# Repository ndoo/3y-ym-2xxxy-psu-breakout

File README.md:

# 3y-ym-2xxxy-psu-breakout

Breakout for 3Y YM-2xxxY series power supply modules

It should also work for any other 50.5mm wide power supply modules from 3Y/FSP, that use PCB finger connectors.

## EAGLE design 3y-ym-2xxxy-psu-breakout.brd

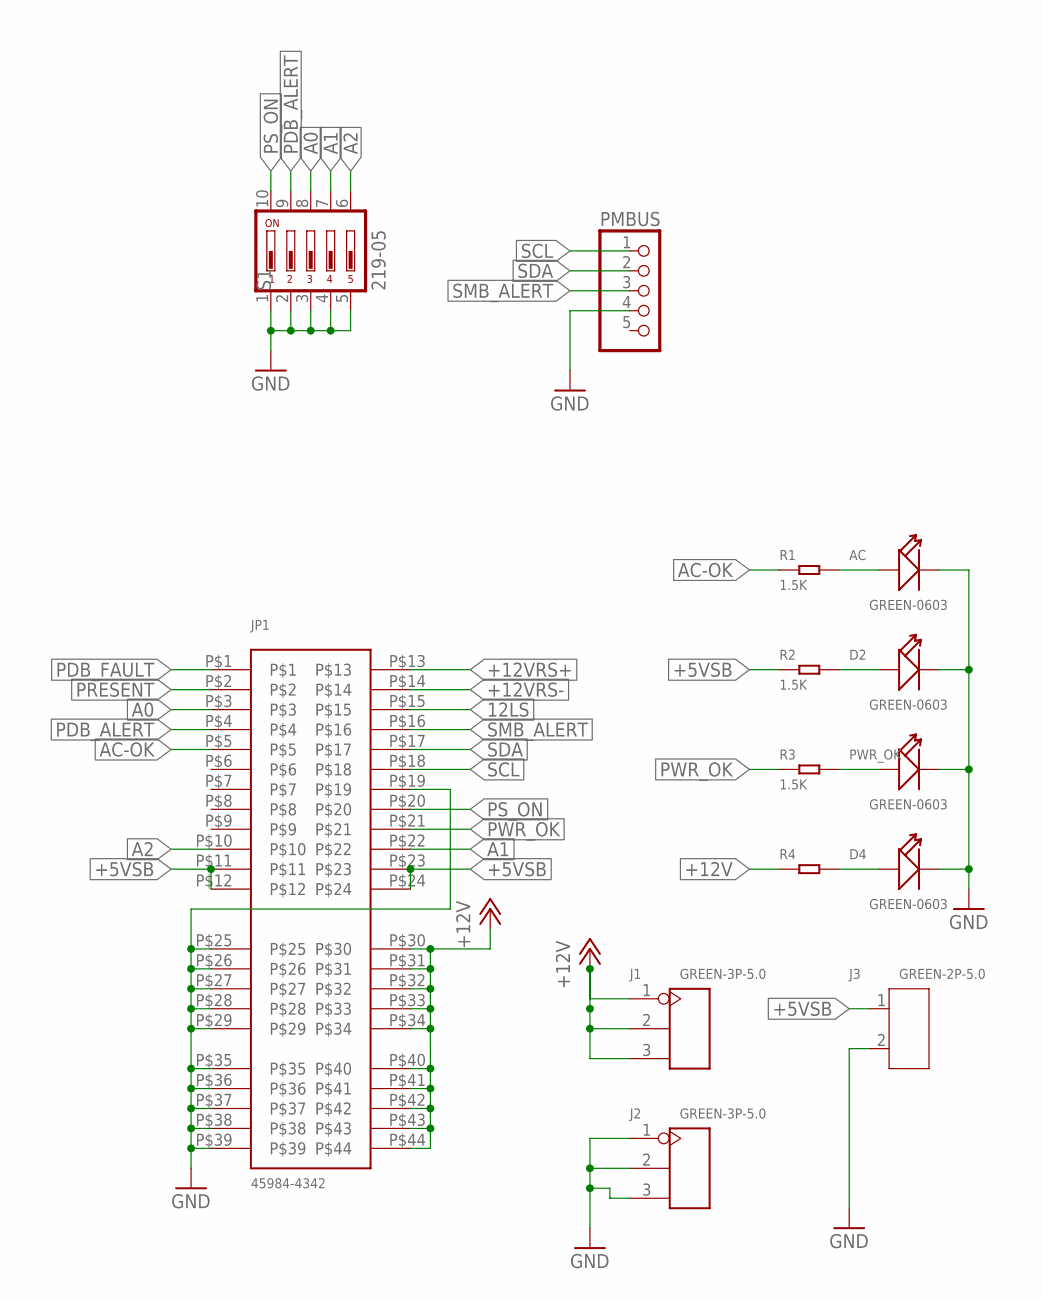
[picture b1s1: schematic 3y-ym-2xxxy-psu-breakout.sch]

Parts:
AC: GREEN-0603; LED-0603
D2, D4: GREEN-0603; LED-0603
J1, J2: GREEN-3P-5.0; H3-5.0-15.5X8.0MM
J3: GREEN-2P-5.0; H2-5.0-10.5X8.0MM
JP1: 45984-4342
PMBUS: PINHD-1X5; 1X05
PWR_OK: GREEN-0603; LED-0603
R1, R2, R3, R4: 1.5K; R0603
S1: 219-05; CTS-219-05

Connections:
12LS: JP1.P$15
+5VSB: J3.1, JP1.P$11, JP1.P$12, JP1.P$23, JP1.P$24, R2.1
+12V: J1.1, J1.2, J1.3, JP1.P$30, JP1.P$31, JP1.P$32, JP1.P$33, JP1.P$34, JP1.P$40, JP1.P$41, JP1.P$42, JP1.P$43, JP1.P$44, R4.1
+12VRS+: JP1.P$13
+12VRS-: JP1.P$14
A0: JP1.P$3, S1.8
A1: JP1.P$22, S1.7
A2: JP1.P$10, S1.6
AC-OK: JP1.P$5, R1.1
GND: AC.-, D2.-, D4.-, J2.1, J2.2, J2.3, J3.2, JP1.P$19, JP1.P$25, JP1.P$26, JP1.P$27, JP1.P$28, JP1.P$29, JP1.P$35, JP1.P$36, JP1.P$37, JP1.P$38, JP1.P$39, PMBUS.4, PWR_OK.-, S1.1, S1.2, S1.3, S1.4, S1.5
unnamed: AC.+, R1.2
unnamed: D2.+, R2.2
unnamed: PWR_OK.+, R3.2
unnamed: D4.+, R4.2
PDB_ALERT: JP1.P$4, S1.9
PDB_FAULT: JP1.P$1
PRESENT: JP1.P$2
PS_ON: JP1.P$20, S1.10
PWR_OK: JP1.P$21, R3.1
SCL: JP1.P$18, PMBUS.1
SDA: JP1.P$17, PMBUS.2
SMB_ALERT: JP1.P$16, PMBUS.3

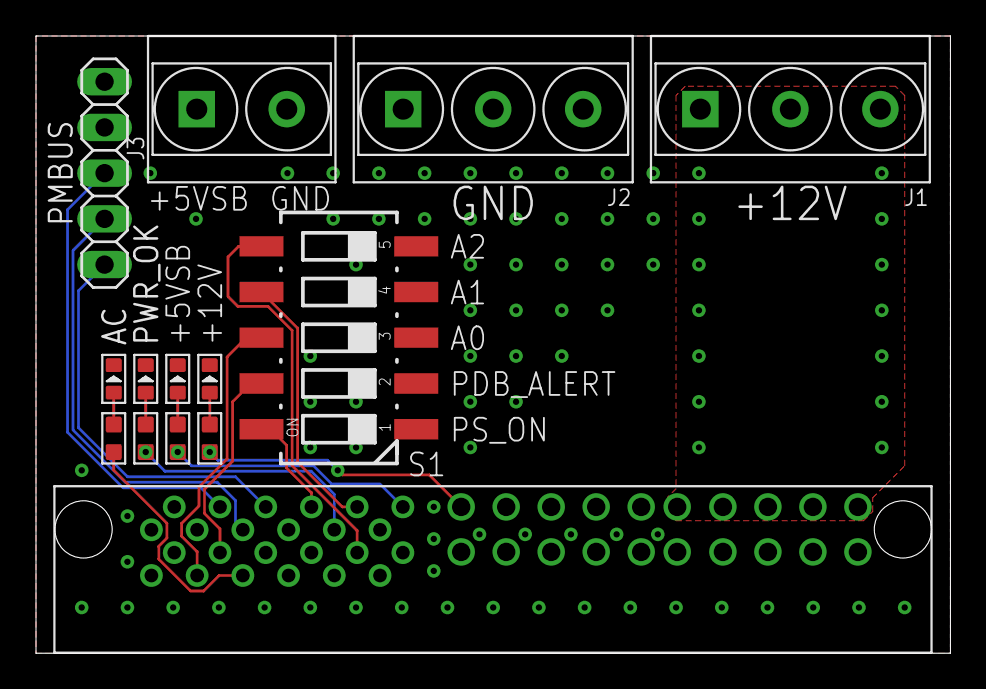
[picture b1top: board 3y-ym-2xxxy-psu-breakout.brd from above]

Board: 2 copper layers, 50.8 x 34.3 mm, 14 parts (0 on the bottom side), 17 nets.

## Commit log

2020-07-08 Initial commit of schematic and board; README update
